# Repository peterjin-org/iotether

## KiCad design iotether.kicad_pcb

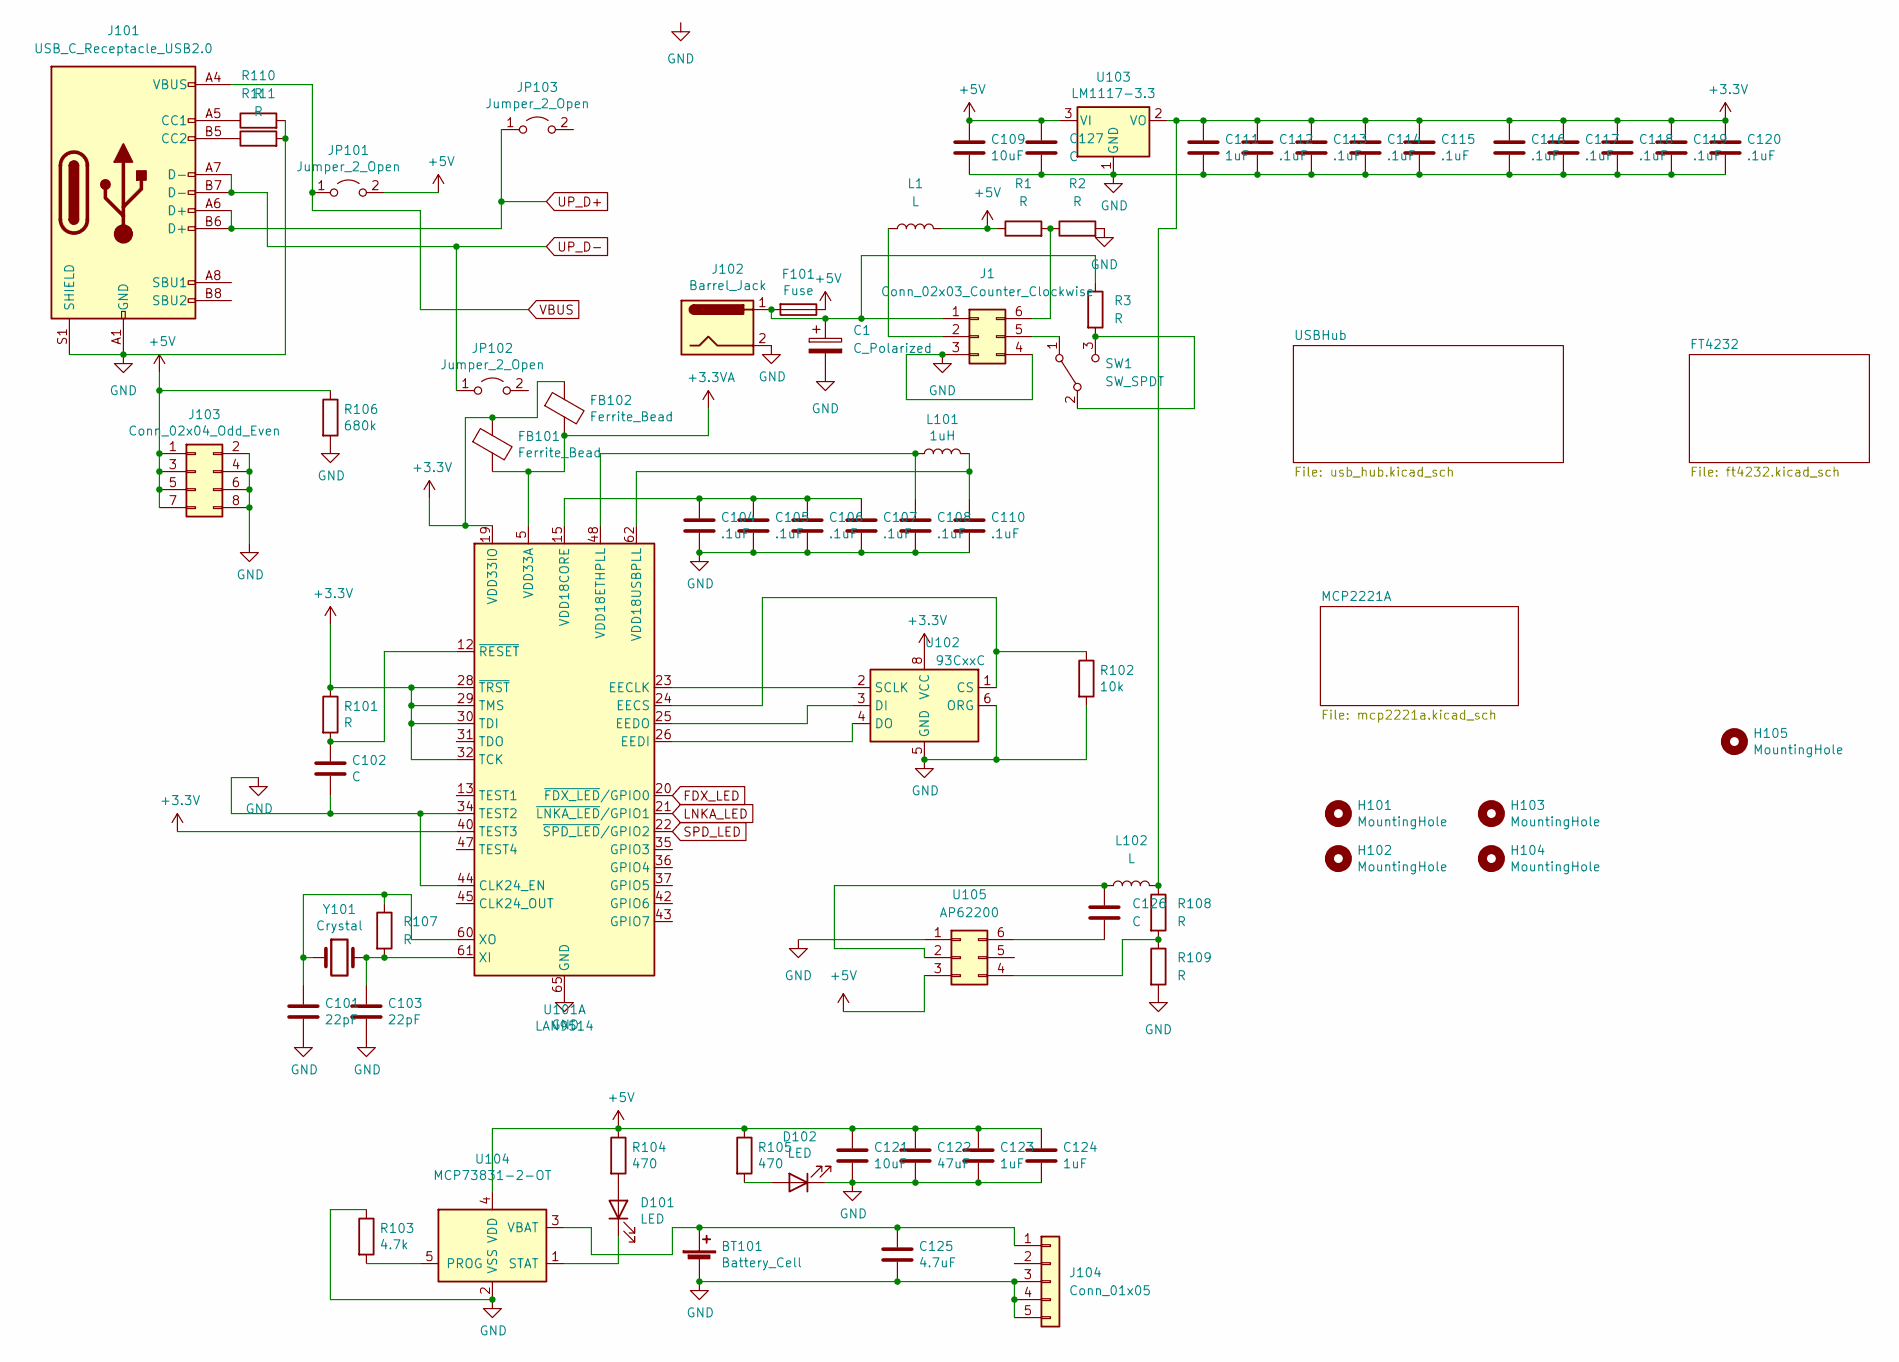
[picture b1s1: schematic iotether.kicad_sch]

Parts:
BT101: Battery_Cell; PinHeader_1x02_P2.54mm_Horizontal
C1: C_Polarized; CP_Radial_D10.0mm_P5.00mm
C101, C103: 22pF; C_0805_2012Metric_Pad1.15x1.40mm_HandSolder
C102: C; C_0805_2012Metric_Pad1.15x1.40mm_HandSolder
C104, C106: .1uF; C_0603_1608Metric_Pad1.08x0.95mm_HandSolder
C105, C107, C108, C110, C112, C113, C114, C115, C116, C117, C118, C119, C120: .1uF; C_0603_1608Metric_Pad1.05x0.95mm_HandSolder
C109: 10uF; C_0805_2012Metric_Pad1.15x1.40mm_HandSolder
C111: 1uF; C_0805_2012Metric_Pad1.15x1.40mm_HandSolder
C121: 10uF; CP_Radial_D8.0mm_P3.50mm
C122: 47uF; CP_Radial_D8.0mm_P3.50mm
C123, C124: 1uF; CP_Radial_D8.0mm_P3.50mm
C125: 4.7uF; CP_Radial_D6.3mm_P2.50mm
C126: C; C_0603_1608Metric
C127: C; CP_Radial_D8.0mm_P3.80mm
D101, D102: LED; LED_1210_3225Metric_Pad1.42x2.65mm_HandSolder
F101: Fuse; Fuse_BelFuse_0ZRE0033FF_L11.4mm_W3.8mm
FB101, FB102: Ferrite_Bead; L_1206_3216Metric_Pad1.22x1.90mm_HandSolder
H101, H102, H103, H104: MountingHole; MountingHole_3.2mm_M3
H105: MountingHole; OSHW-Logo2_7.3x6mm_SilkScreen
J1: Conn_02x03_Counter_Clockwise; SOT-563
J101: USB_C_Receptacle_USB2.0; USB_C_Receptacle_GCT_USB4105-xx-A_16P_TopMnt_Horizontal
J102: Barrel_Jack; BarrelJack_Horizontal
J103: Conn_02x04_Odd_Even; PinHeader_2x04_P2.54mm_Vertical
J104: Conn_01x05; 009155003541006
JP101, JP102, JP103: Jumper_2_Open; R_0603_1608Metric
L1: L; L_Radial_D12.5mm_P7.00mm_Fastron_09HCP
L101: 1uH; L_1206_3216Metric_Pad1.42x1.75mm_HandSolder
L102: L; L_1210_3225Metric_Pad1.42x2.65mm_HandSolder
R1, R2, R3, R108, R109, R110, R111: R; R_0603_1608Metric
R101: R; R_0603_1608Metric_Pad1.05x0.95mm_HandSolder
R102: 10k; R_0603_1608Metric_Pad1.05x0.95mm_HandSolder
R103: 4.7k; R_0603_1608Metric_Pad1.05x0.95mm_HandSolder
R104, R105: 470; R_0603_1608Metric_Pad1.05x0.95mm_HandSolder
R106: 680k; R_0603_1608Metric_Pad0.98x0.95mm_HandSolder
R107: R; R_0805_2012Metric
SW1: SW_SPDT; PinSocket_1x03_P2.54mm_Vertical
U101: LAN9514; QFN-64-1EP_9x9mm_P0.5mm_EP6x6mm
U102: 93CxxC; DIP-8_W7.62mm_Socket
U103: LM1117-3.3; SOT-223-3_TabPin2
U104: MCP73831-2-OT; SOT-23-5
U105: AP62200; SOT-23-6
Y101: Crystal; Crystal_HC49-U_Vertical

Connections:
+3.3VA: FB101.2, FB102.2, U101.5 (VDD33A), U101.10 (VDD33A), U101.49 (VDD33A), U101.51 (VDD33A), U101.54 (VDD33A), U101.57 (VDD33A), U101.64 (VDD33A); also elsewhere on the board
+3V3: C111.1, C112.1, C113.1, C114.1, C115.1, C116.1, C117.1, C118.1, C119.1, C120.1, FB101.1, FB102.1, L102.2, R101.1, R108.1, U101.19 (VDD33IO), U101.27 (VDD33IO), U101.28 (~TRST), U101.29 (TMS), U101.30 (TDI), U101.32 (TCK), U101.33 (VDD33IO), U101.39 (VDD33IO), U101.40 (TEST3), U101.46 (VDD33IO), U102.8 (VCC), U103.2 (VO); also elsewhere on the board
+5V: C109.1, C121.1, C122.1, C123.1, C124.1, C127.1, F101.1, J103.1, J103.3, J103.5, J103.7, JP101.2 (B), L1.2, R1.1, R104.1, R105.1, R106.1, U103.3 (VI), U104.4 (VDD), U105.3; also elsewhere on the board
FDX_LED: U101.20 (~FDX_LED/GPIO0); also elsewhere on the board
GND: BT101.2 (-), C1.2, C101.2, C102.2, C103.2, C104.2, C105.2, C106.2, C107.2, C108.2, C109.2, C110.2, C111.2, C112.2, C113.2, C114.2, C115.2, C116.2, C117.2, C118.2, C119.2, C120.2, C121.2, C122.2, C123.2, C124.2, C125.2, C127.2, D102.1 (K), J1.3, J1.4, J101.A1 (GND), J101.A12 (GND), J101.B1 (GND), J101.B12 (GND), J101.S1 (SHIELD), J102.2, J103.2, J103.4, J103.6, J103.8, J104.3, J104.4, J104.5, R2.2, R102.2, R103.1, R106.2, R109.2, R110.2, R111.2, U101.34 (TEST2), U101.44 (CLK24_EN), U101.65 (GND), U102.5 (GND), U102.6 (ORG), U103.1 (GND), U104.2 (VSS), U105.1; also elsewhere on the board
LNKA_LED: U101.21 (~LNKA_LED/GPIO1); also elsewhere on the board
unnamed: BT101.1 (+), C125.1, J104.1, U104.3 (VBAT)
unnamed: C1.1, F101.2, J1.1, J102.1, R3.1
unnamed: C101.1, R107.1, U101.60 (XO), Y101.1
unnamed: C102.1, R101.2, U101.12 (~RESET)
unnamed: C103.1, R107.2, U101.61 (XI), Y101.2
unnamed: C104.1, C105.1, C106.1, C107.1, U101.15 (VDD18CORE), U101.38 (VDD18CORE)
unnamed: C108.1, L101.1, U101.48 (VDD18ETHPLL)
unnamed: C110.1, L101.2, U101.62 (VDD18USBPLL)
unnamed: C126.1, L102.1, U105.2
unnamed: C126.2, U105.6
unnamed: D101.1 (K), U104.1 (STAT)
unnamed: D101.2 (A), R104.2
unnamed: D102.2 (A), R105.2
unnamed: J1.2, L1.1
unnamed: J1.5, SW1.1 (A)
unnamed: J1.6, R1.2, R2.1
unnamed: J101.A5 (CC1), R110.1
unnamed: J101.B5 (CC2), R111.1
unnamed: R3.2, SW1.2 (B), SW1.3 (C)
unnamed: R102.1, U101.24 (EECS), U102.1 (CS)
unnamed: R103.2, U104.5 (PROG)
unnamed: R108.2, R109.1, U105.4
unnamed: U101.23 (EECLK), U102.2 (SCLK)
unnamed: U101.25 (EEDO), U102.3 (DI)
unnamed: U101.26 (EEDI), U102.4 (DO)
SPD_LED: U101.22 (~SPD_LED/GPIO2); also elsewhere on the board
UP_D+: J101.A6 (D+), J101.B6 (D+), JP103.1 (A); also elsewhere on the board
UP_D-: J101.A7 (D-), J101.B7 (D-), JP102.1 (A); also elsewhere on the board
VBUS: J101.A4 (VBUS), J101.A9 (VBUS), J101.B4 (VBUS), J101.B9 (VBUS), JP101.1 (A); also elsewhere on the board

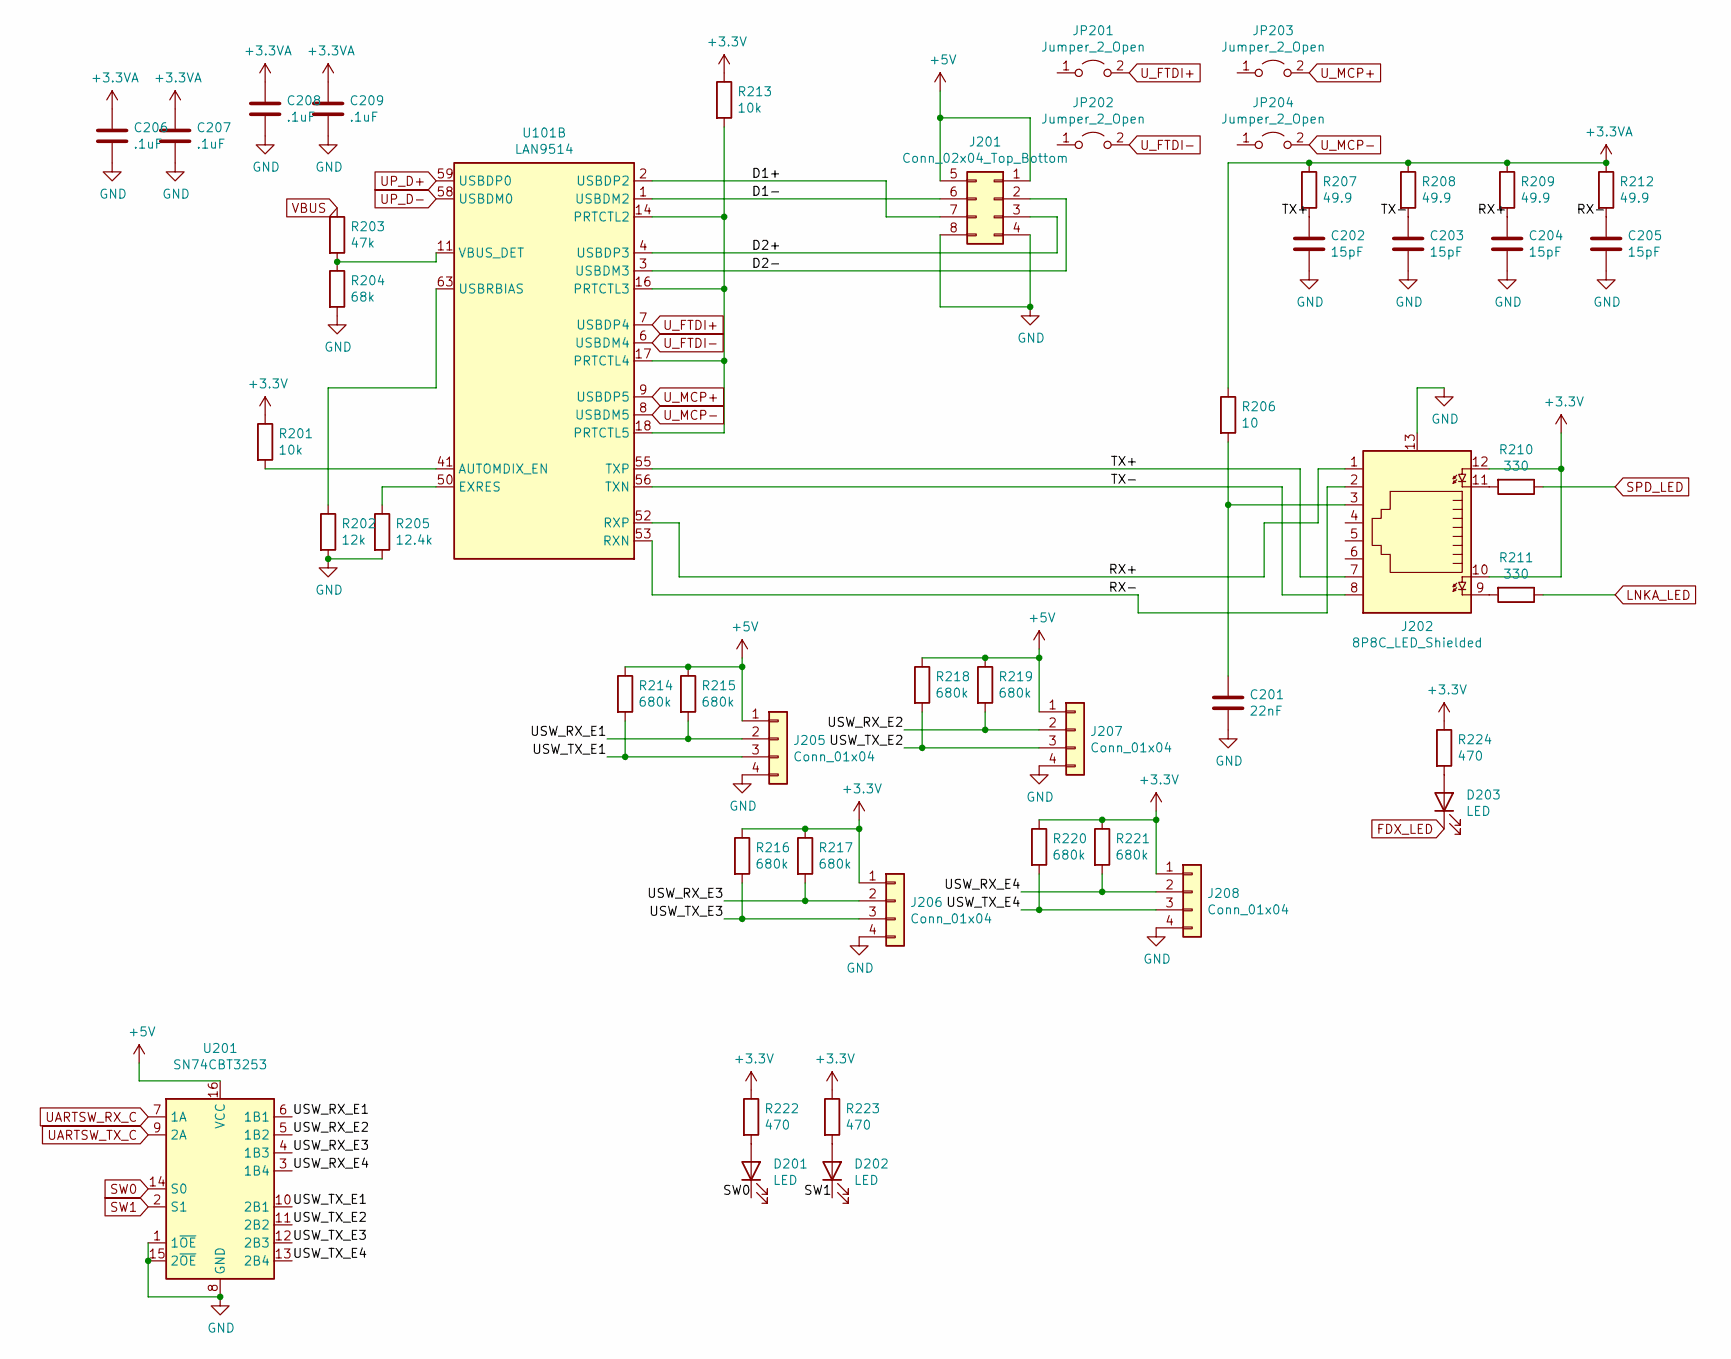
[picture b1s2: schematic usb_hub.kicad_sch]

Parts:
C201: 22nF; C_0603_1608Metric_Pad1.05x0.95mm_HandSolder
C202, C203, C204, C205: 15pF; C_0603_1608Metric_Pad1.05x0.95mm_HandSolder
C206, C207, C208, C209: .1uF; C_0603_1608Metric_Pad1.08x0.95mm_HandSolder
D201, D202, D203: LED; LED_0603_1608Metric_Pad1.05x0.95mm_HandSolder
J201: Conn_02x04_Top_Bottom; USB_A_Wuerth_61400826021_Horizontal_Stacked
J202: 8P8C_LED_Shielded; RJ45_Cetus_J1B1211CCD_Horizontal
J205, J206, J207, J208: Conn_01x04; PinHeader_1x04_P2.54mm_Vertical
JP201, JP202, JP203, JP204: Jumper_2_Open; R_0603_1608Metric
R201, R213: 10k; R_0603_1608Metric_Pad1.05x0.95mm_HandSolder
R202: 12k; R_0603_1608Metric_Pad1.05x0.95mm_HandSolder
R203: 47k; R_0603_1608Metric_Pad1.05x0.95mm_HandSolder
R204: 68k; R_0603_1608Metric_Pad1.05x0.95mm_HandSolder
R205: 12.4k; R_0603_1608Metric_Pad1.05x0.95mm_HandSolder
R206: 10; R_0603_1608Metric_Pad1.05x0.95mm_HandSolder
R207, R208, R209, R212: 49.9; R_0603_1608Metric_Pad1.05x0.95mm_HandSolder
R210, R211: 330; R_0603_1608Metric_Pad0.98x0.95mm_HandSolder
R214, R215, R216, R217, R218, R219, R220, R221: 680k; R_0603_1608Metric_Pad0.98x0.95mm_HandSolder
R222, R223, R224: 470; R_0603_1608Metric_Pad0.98x0.95mm_HandSolder
U101: LAN9514; QFN-64-1EP_9x9mm_P0.5mm_EP6x6mm
U201: SN74CBT3253; SOIC-16_3.9x9.9mm_P1.27mm

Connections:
+3.3VA: C206.1, C207.1, C208.1, C209.1, R206.1, R207.1, R208.1, R209.1, R212.1; also elsewhere on the board
+3V3: J202.10, J202.12, J206.1, J208.1, R201.1, R213.1, R216.1, R217.1, R220.1, R221.1, R222.1, R223.1, R224.1; also elsewhere on the board
+5V: J201.1, J201.5, J205.1, J207.1, R214.1, R215.1, R218.1, R219.1, U201.16 (VCC); also elsewhere on the board
/USBHub/D1+: J201.7, U101.2 (USBDP2)
/USBHub/D1-: J201.6, U101.1 (USBDM2)
/USBHub/D2+: J201.3, U101.4 (USBDP3)
/USBHub/D2-: J201.2, U101.3 (USBDM3)
/USBHub/RX+: C204.1, J202.1, R209.2, U101.52 (RXP)
/USBHub/RX-: C205.1, J202.2, R212.2, U101.53 (RXN)
/USBHub/TX+: C202.1, J202.7, R207.2, U101.55 (TXP)
/USBHub/TX-: C203.1, J202.8, R208.2, U101.56 (TXN)
/USBHub/USW_RX_E1: J205.2, R215.2, U201.6 (1B1)
/USBHub/USW_RX_E2: J207.2, R219.2, U201.5 (1B2)
/USBHub/USW_RX_E3: J206.2, R217.2, U201.4 (1B3)
/USBHub/USW_RX_E4: J208.2, R221.2, U201.3 (1B4)
/USBHub/USW_TX_E1: J205.3, R214.2, U201.10 (2B1)
/USBHub/USW_TX_E2: J207.3, R218.2, U201.11 (2B2)
/USBHub/USW_TX_E3: J206.3, R216.2, U201.12 (2B3)
/USBHub/USW_TX_E4: J208.3, R220.2, U201.13 (2B4)
FDX_LED: D203.1 (K); also elsewhere on the board
GND: C201.2, C202.2, C203.2, C204.2, C205.2, C206.2, C207.2, C208.2, C209.2, J201.4, J201.8, J202.13, J205.4, J206.4, J207.4, J208.4, R202.2, R204.2, R205.2, U201.1 (1~OE), U201.8 (GND), U201.15 (2~OE); also elsewhere on the board
LNKA_LED: R211.1; also elsewhere on the board
unnamed: C201.1, J202.3, R206.2
unnamed: D201.2 (A), R222.2
unnamed: D202.2 (A), R223.2
unnamed: D203.2 (A), R224.2
unnamed: J202.9, R211.2
unnamed: J202.11, R210.2
unnamed: R201.2, U101.41 (AUTOMDIX_EN)
unnamed: R202.1, U101.63 (USBRBIAS)
unnamed: R203.2, R204.1, U101.11 (VBUS_DET)
unnamed: R205.1, U101.50 (EXRES)
unnamed: R213.2, U101.14 (PRTCTL2), U101.16 (PRTCTL3), U101.17 (PRTCTL4), U101.18 (PRTCTL5)
SPD_LED: R210.1; also elsewhere on the board
SW0: D201.1 (K), U201.14 (S0); also elsewhere on the board
SW1: D202.1 (K), U201.2 (S1); also elsewhere on the board
UARTSW_RX_C: U201.7 (1A); also elsewhere on the board
UARTSW_TX_C: U201.9 (2A); also elsewhere on the board
UP_D+: U101.59 (USBDP0); also elsewhere on the board
UP_D-: U101.58 (USBDM0); also elsewhere on the board
U_FTDI+: JP201.2 (B), U101.7 (USBDP4); also elsewhere on the board
U_FTDI-: JP202.2 (B), U101.6 (USBDM4); also elsewhere on the board
U_MCP+: JP203.2 (B), U101.9 (USBDP5); also elsewhere on the board
U_MCP-: JP204.2 (B), U101.8 (USBDM5); also elsewhere on the board
VBUS: R203.1; also elsewhere on the board

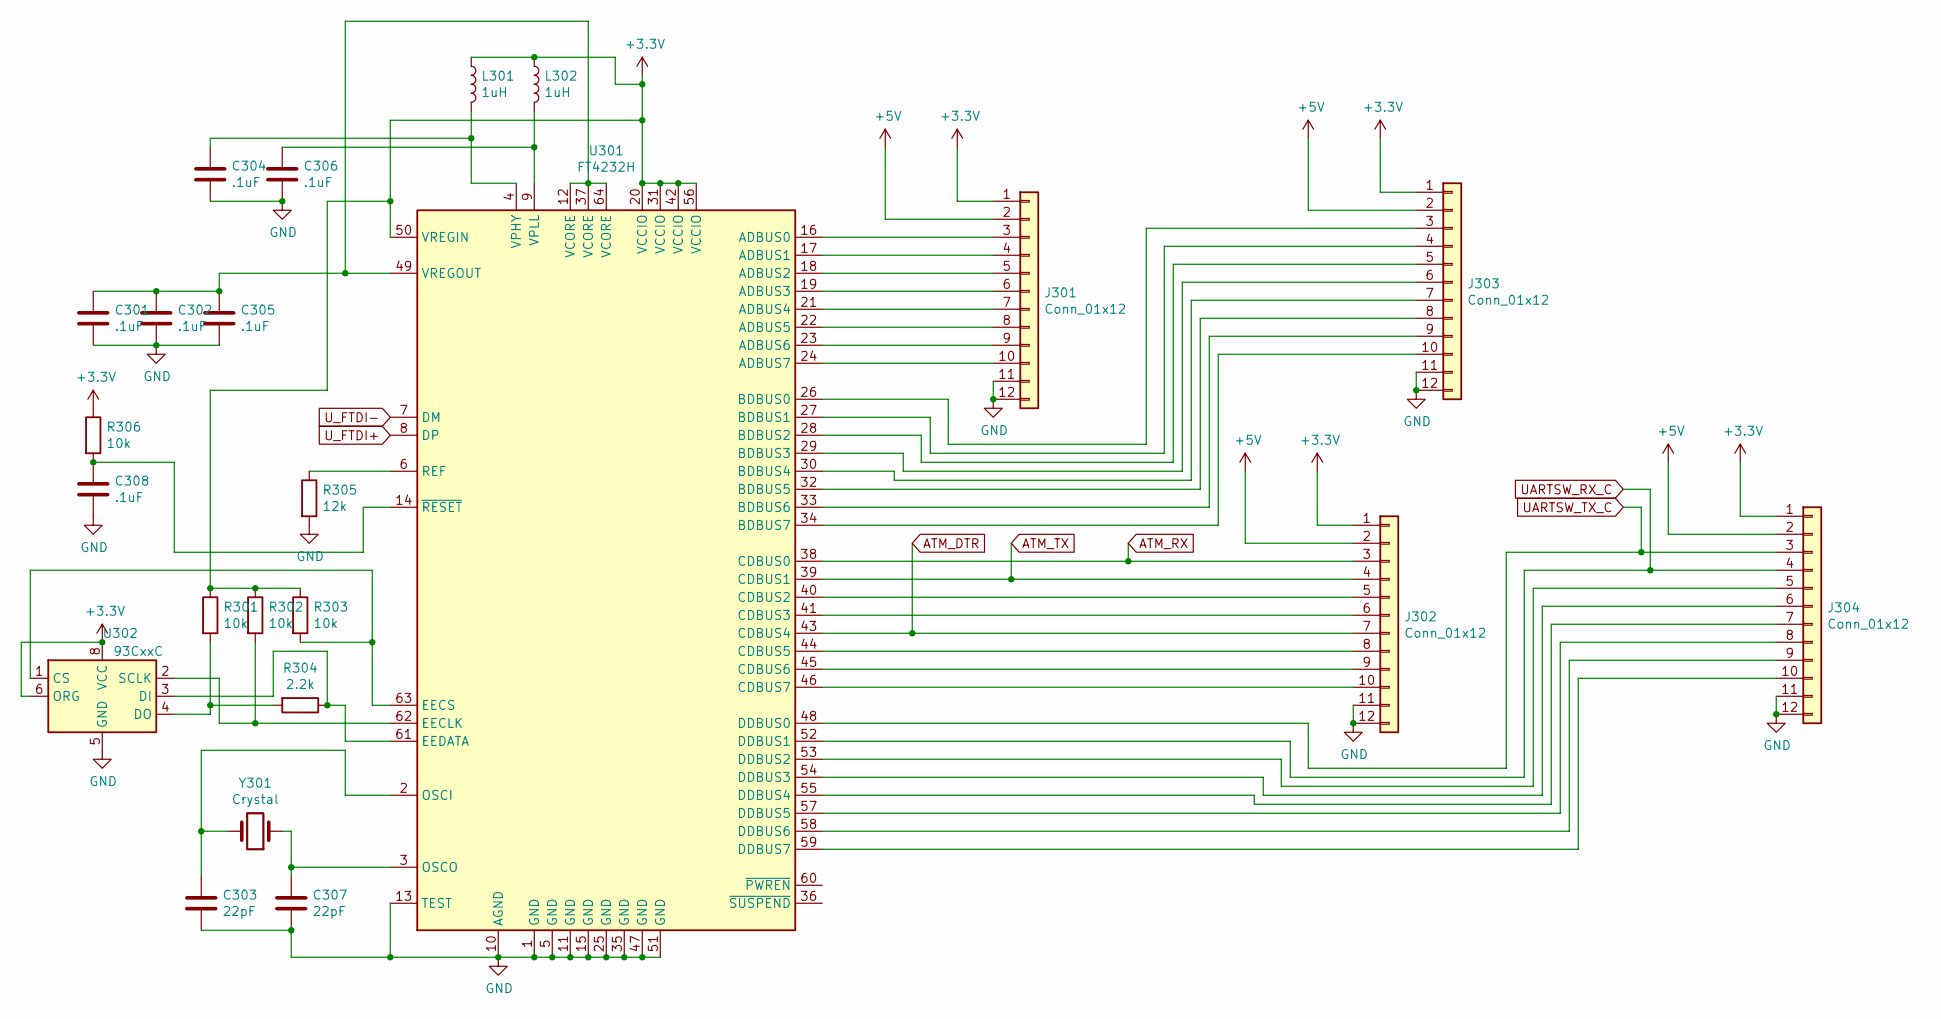
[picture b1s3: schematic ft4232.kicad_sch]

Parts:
C301, C302, C304, C305, C306, C308: .1uF; C_0603_1608Metric_Pad1.05x0.95mm_HandSolder
C303, C307: 22pF; C_0805_2012Metric_Pad1.15x1.40mm_HandSolder
J301, J302, J303, J304: Conn_01x12; PinHeader_2x06_P2.54mm_Vertical
L301, L302: 1uH; L_1206_3216Metric_Pad1.42x1.75mm_HandSolder
R301, R302, R303, R306: 10k; R_0603_1608Metric_Pad1.05x0.95mm_HandSolder
R304: 2.2k; R_0603_1608Metric_Pad0.98x0.95mm_HandSolder
R305: 12k; R_0603_1608Metric_Pad1.05x0.95mm_HandSolder
U301: FT4232H; LQFP-64_10x10mm_P0.5mm
U302: 93CxxC; DIP-8_W7.62mm_Socket
Y301: Crystal; Crystal_HC49-U_Vertical

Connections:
+3V3: J301.1, J302.1, J303.1, J304.1, L301.1, L302.1, R301.1, R302.1, R303.1, R306.1, U301.20 (VCCIO), U301.31 (VCCIO), U301.42 (VCCIO), U301.50 (VREGIN), U301.56 (VCCIO), U302.6 (ORG), U302.8 (VCC); also elsewhere on the board
+5V: J301.2, J302.2, J303.2, J304.2; also elsewhere on the board
ATM_DTR: J302.7, U301.43 (CDBUS4); also elsewhere on the board
ATM_RX: J302.3, U301.38 (CDBUS0); also elsewhere on the board
ATM_TX: J302.4, U301.39 (CDBUS1); also elsewhere on the board
GND: C301.2, C302.2, C303.2, C304.2, C305.2, C306.2, C307.2, C308.2, J301.11, J301.12, J302.11, J302.12, J303.11, J303.12, J304.11, J304.12, R305.2, U301.1 (GND), U301.5 (GND), U301.10 (AGND), U301.11 (GND), U301.13 (TEST), U301.15 (GND), U301.25 (GND), U301.35 (GND), U301.47 (GND), U301.51 (GND), U302.5 (GND); also elsewhere on the board
unnamed: C301.1, C302.1, C305.1, U301.12 (VCORE), U301.37 (VCORE), U301.49 (VREGOUT), U301.64 (VCORE)
unnamed: C303.1, U301.2 (OSCI), Y301.2
unnamed: C304.1, L301.2, U301.4 (VPHY)
unnamed: C306.1, L302.2, U301.9 (VPLL)
unnamed: C307.1, U301.3 (OSCO), Y301.1
unnamed: C308.1, R306.2, U301.14 (~RESET)
unnamed: J301.3, U301.16 (ADBUS0)
unnamed: J301.4, U301.17 (ADBUS1)
unnamed: J301.5, U301.18 (ADBUS2)
unnamed: J301.6, U301.19 (ADBUS3)
unnamed: J301.7, U301.21 (ADBUS4)
unnamed: J301.8, U301.22 (ADBUS5)
unnamed: J301.9, U301.23 (ADBUS6)
unnamed: J301.10, U301.24 (ADBUS7)
unnamed: J302.5, U301.40 (CDBUS2)
unnamed: J302.6, U301.41 (CDBUS3)
unnamed: J302.8, U301.44 (CDBUS5)
unnamed: J302.9, U301.45 (CDBUS6)
unnamed: J302.10, U301.46 (CDBUS7)
unnamed: J303.3, U301.26 (BDBUS0)
unnamed: J303.4, U301.27 (BDBUS1)
unnamed: J303.5, U301.28 (BDBUS2)
unnamed: J303.6, U301.29 (BDBUS3)
unnamed: J303.7, U301.30 (BDBUS4)
unnamed: J303.8, U301.32 (BDBUS5)
unnamed: J303.9, U301.33 (BDBUS6)
unnamed: J303.10, U301.34 (BDBUS7)
unnamed: J304.5, U301.53 (DDBUS2)
unnamed: J304.6, U301.54 (DDBUS3)
unnamed: J304.7, U301.55 (DDBUS4)
unnamed: J304.8, U301.57 (DDBUS5)
unnamed: J304.9, U301.58 (DDBUS6)
unnamed: J304.10, U301.59 (DDBUS7)
unnamed: R301.2, R304.2, U302.4 (DO)
unnamed: R302.2, U301.62 (EECLK), U302.2 (SCLK)
unnamed: R303.2, U301.63 (EECS), U302.1 (CS)
unnamed: R304.1, U301.61 (EEDATA), U302.3 (DI)
unnamed: R305.1, U301.6 (REF)
UARTSW_RX_C: J304.4, U301.52 (DDBUS1); also elsewhere on the board
UARTSW_TX_C: J304.3, U301.48 (DDBUS0); also elsewhere on the board
U_FTDI+: U301.8 (DP); also elsewhere on the board
U_FTDI-: U301.7 (DM); also elsewhere on the board

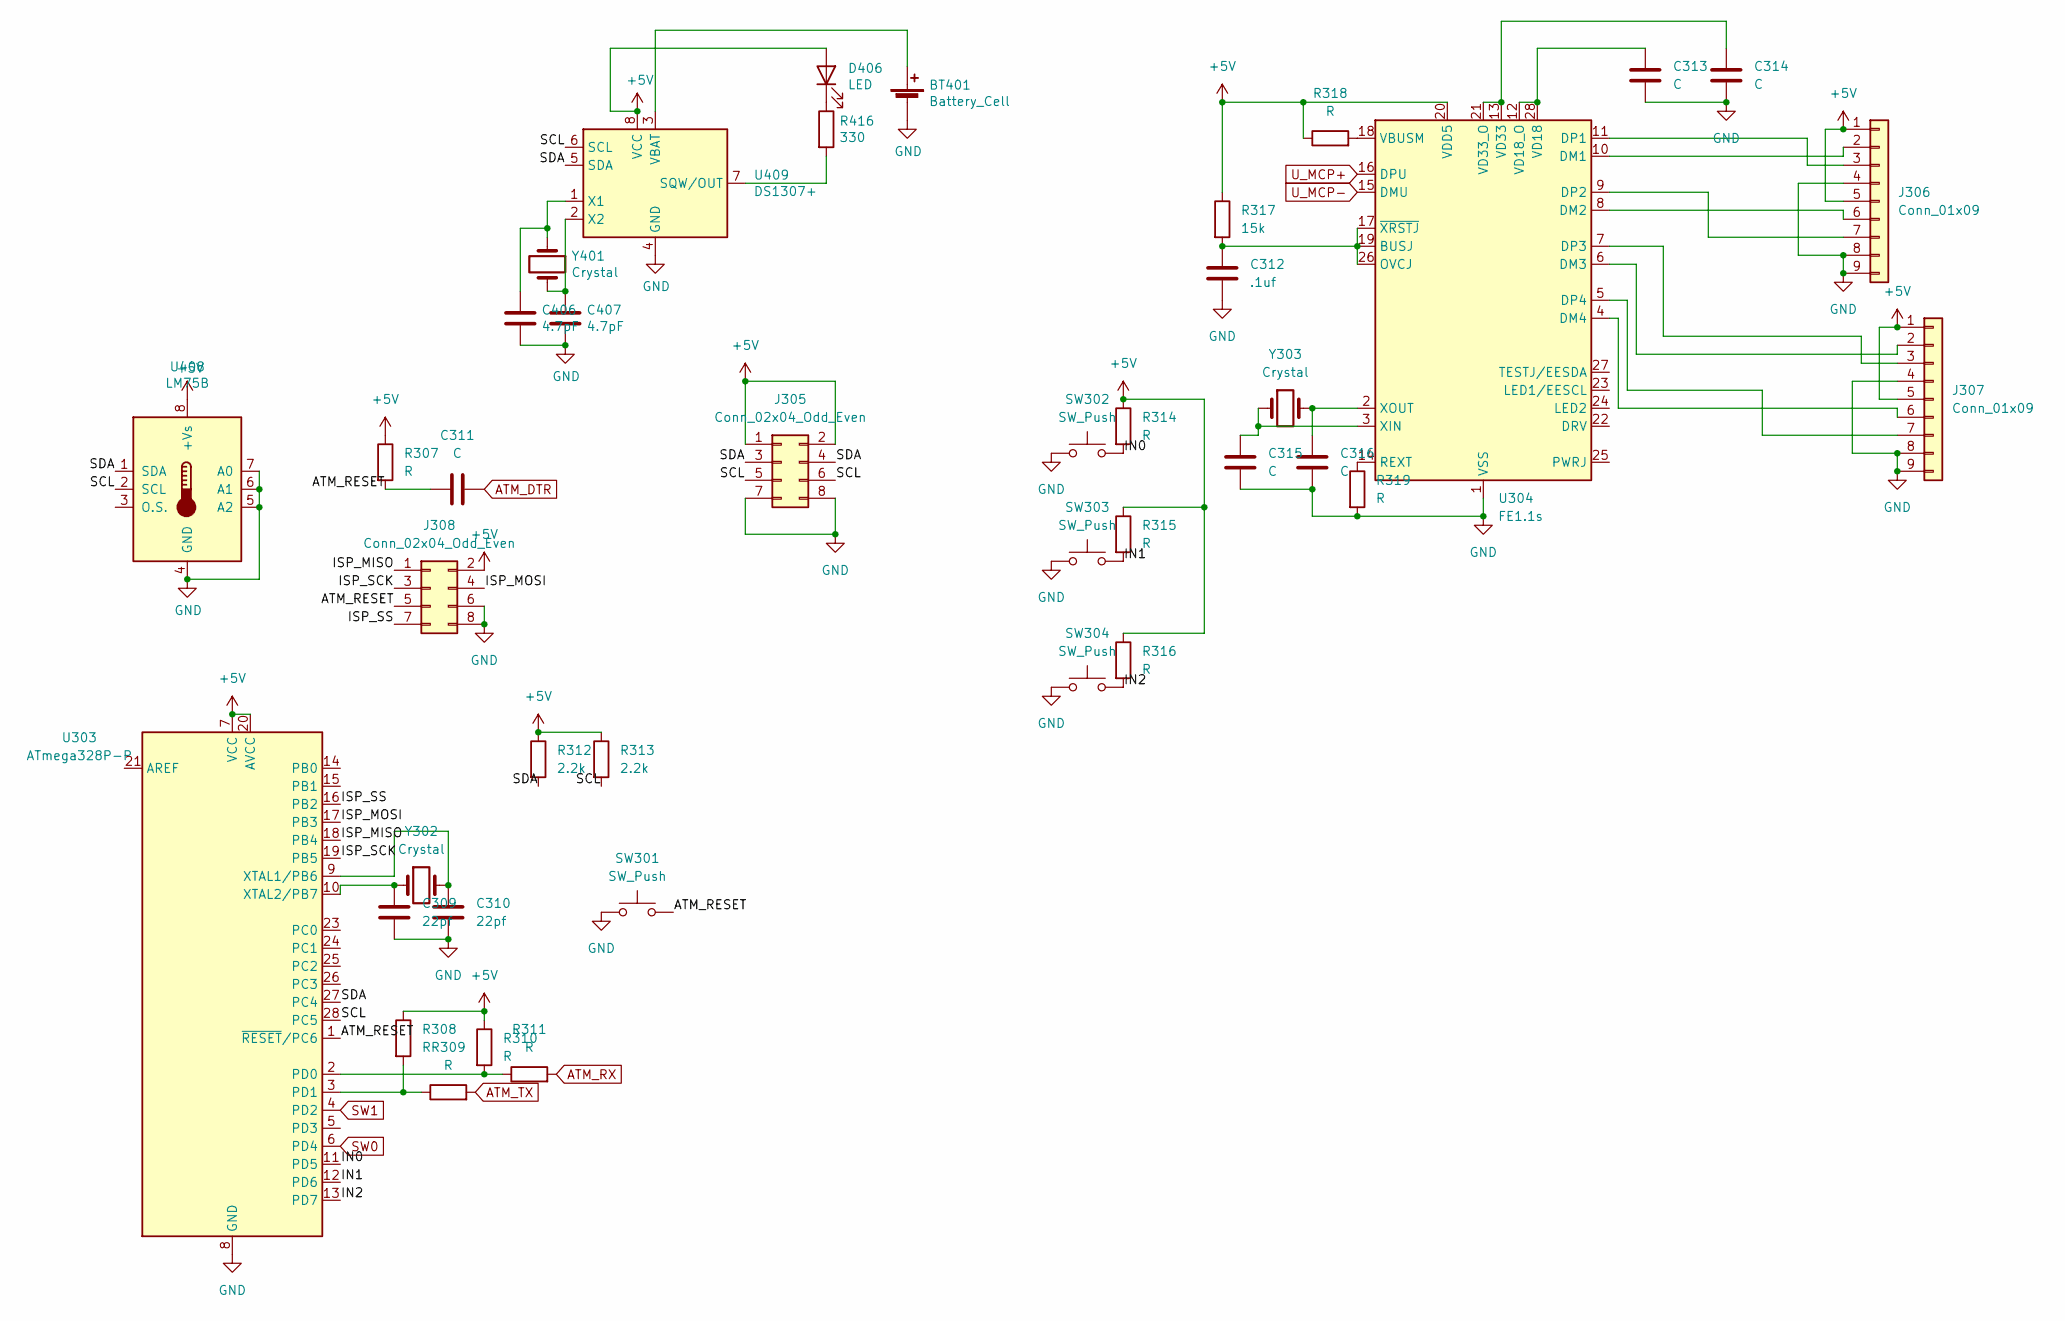
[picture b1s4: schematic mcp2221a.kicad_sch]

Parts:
BT401: Battery_Cell; PinHeader_1x02_P2.54mm_Vertical
C309, C310: 22pf; C_0805_2012Metric_Pad1.18x1.45mm_HandSolder
C311: C; C_0603_1608Metric_Pad1.08x0.95mm_HandSolder
C312: .1uf; C_0603_1608Metric_Pad1.08x0.95mm_HandSolder
C313, C314, C315, C316: C; C_0805_2012Metric_Pad1.18x1.45mm_HandSolder
C406, C407: 4.7pF; C_0603_1608Metric_Pad1.08x0.95mm_HandSolder
D406: LED; LED_0603_1608Metric_Pad1.05x0.95mm_HandSolder
J305, J308: Conn_02x04_Odd_Even; PinHeader_2x04_P2.54mm_Vertical
J306, J307: Conn_01x09; USB_A_Wuerth_61400826021_Horizontal_Stacked
R307, R308, R309, R310, R311, R314, R315, R316, R318, R319: R; R_0603_1608Metric_Pad0.98x0.95mm_HandSolder
R312, R313: 2.2k; R_0603_1608Metric_Pad0.98x0.95mm_HandSolder
R317: 15k; R_0603_1608Metric_Pad0.98x0.95mm_HandSolder
R416: 330; R_0603_1608Metric_Pad0.98x0.95mm_HandSolder
SW301, SW302, SW303, SW304: SW_Push; SW_PUSH_6mm
U303: ATmega328P-P; DIP-28_W7.62mm
U304: FE1.1s; SSOP-28_3.9x9.9mm_P0.635mm
U408: LM75B; SOIC-8_3.9x4.9mm_P1.27mm
U409: DS1307+; SOIC-8_3.9x4.9mm_P1.27mm
Y302, Y303: Crystal; Crystal_HC49-U_Vertical
Y401: Crystal; Crystal_C26-LF_D2.1mm_L6.5mm_Horizontal

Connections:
+5V: D406.2 (A), J305.1, J305.2, J306.1, J306.5, J307.1, J307.5, J308.2, R307.1, R308.1, R310.1, R312.1, R313.1, R314.1, R315.1, R316.1, R317.1, R318.1, U303.7 (VCC), U303.20 (AVCC), U304.20 (VDD5), U408.8 (+Vs), U409.8 (VCC); also elsewhere on the board
/MCP2221A/ATM_RESET: C311.1, J308.5, R307.2, SW301.2, U303.1 (~RESET/PC6)
/MCP2221A/IN0: R314.2, SW302.2, U303.11 (PD5)
/MCP2221A/IN1: R315.2, SW303.2, U303.12 (PD6)
/MCP2221A/IN2: R316.2, SW304.2, U303.13 (PD7)
/MCP2221A/ISP_MISO: J308.1, U303.18 (PB4)
/MCP2221A/ISP_MOSI: J308.4, U303.17 (PB3)
/MCP2221A/ISP_SCK: J308.3, U303.19 (PB5)
/MCP2221A/ISP_SS: J308.7, U303.16 (PB2)
/MCP2221A/SCL: J305.5, J305.6, R313.2, U303.28 (PC5), U408.2 (SCL), U409.6 (SCL)
/MCP2221A/SDA: J305.3, J305.4, R312.2, U303.27 (PC4), U408.1 (SDA), U409.5 (SDA)
ATM_DTR: C311.2; also elsewhere on the board
ATM_RX: R311.2; also elsewhere on the board
ATM_TX: R309.2; also elsewhere on the board
GND: BT401.2 (-), C309.2, C310.2, C312.2, C313.2, C314.2, C315.2, C316.2, C406.2, C407.2, J305.7, J305.8, J306.4, J306.8, J306.9, J307.4, J307.8, J307.9, J308.6, J308.8, R319.2, SW301.1, SW302.1, SW303.1, SW304.1, U303.8 (GND), U303.22 (GND), U304.1 (VSS), U408.4 (GND), U408.5 (A2), U408.6 (A1), U408.7 (A0), U409.4 (GND); also elsewhere on the board
unnamed: BT401.1 (+), U409.3 (VBAT)
unnamed: C309.1, U303.10 (XTAL2/PB7), Y302.1
unnamed: C310.1, U303.9 (XTAL1/PB6), Y302.2
unnamed: C312.1, R317.2, U304.17 (~XRSTJ), U304.19 (BUSJ), U304.26 (OVCJ)
unnamed: C313.1, U304.12 (VD18_O), U304.28 (VD18)
unnamed: C314.1, U304.13 (VD33), U304.21 (VD33_O)
unnamed: C315.1, U304.3 (XIN), Y303.1
unnamed: C316.1, U304.2 (XOUT), Y303.2
unnamed: C406.1, U409.1 (X1), Y401.1
unnamed: C407.1, U409.2 (X2), Y401.2
unnamed: D406.1 (K), R416.1
unnamed: J306.2, U304.10 (DM1)
unnamed: J306.3, U304.11 (DP1)
unnamed: J306.6, U304.8 (DM2)
unnamed: J306.7, U304.9 (DP2)
unnamed: J307.2, U304.6 (DM3)
unnamed: J307.3, U304.7 (DP3)
unnamed: J307.6, U304.4 (DM4)
unnamed: J307.7, U304.5 (DP4)
unnamed: R308.2, R309.1, U303.3 (PD1)
unnamed: R310.2, R311.1, U303.2 (PD0)
unnamed: R318.2, U304.18 (VBUSM)
unnamed: R319.1, U304.14 (REXT)
unnamed: R416.2, U409.7 (SQW/OUT)
SW0: U303.6 (PD4); also elsewhere on the board
SW1: U303.4 (PD2); also elsewhere on the board
U_MCP+: U304.16 (DPU); also elsewhere on the board
U_MCP-: U304.15 (DMU); also elsewhere on the board

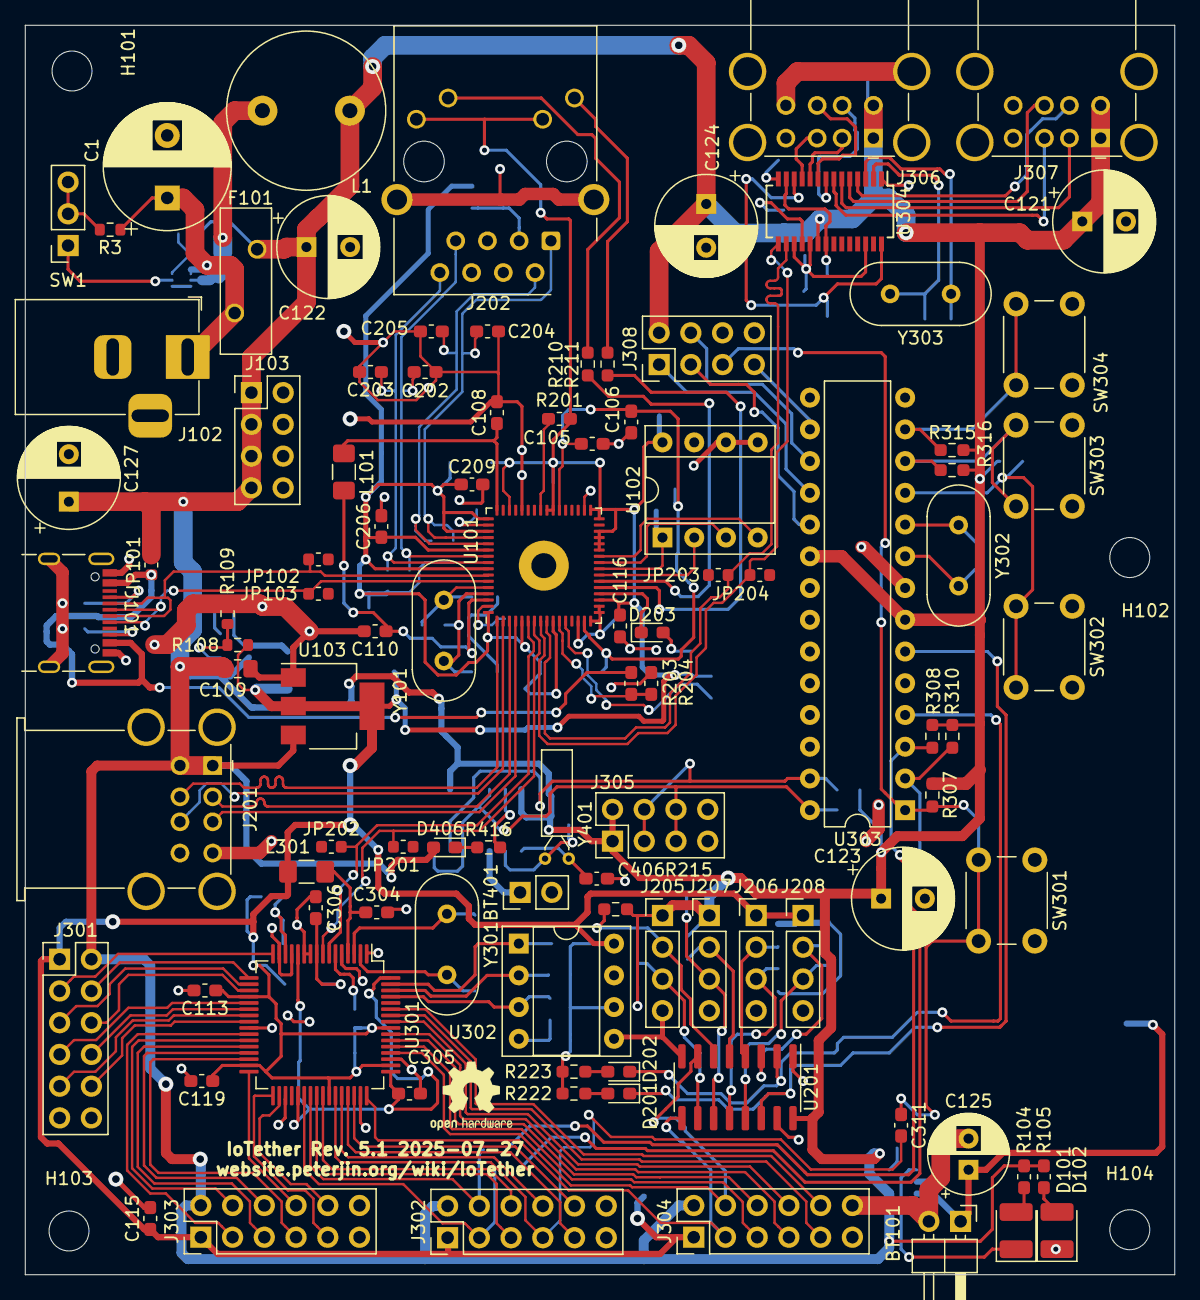
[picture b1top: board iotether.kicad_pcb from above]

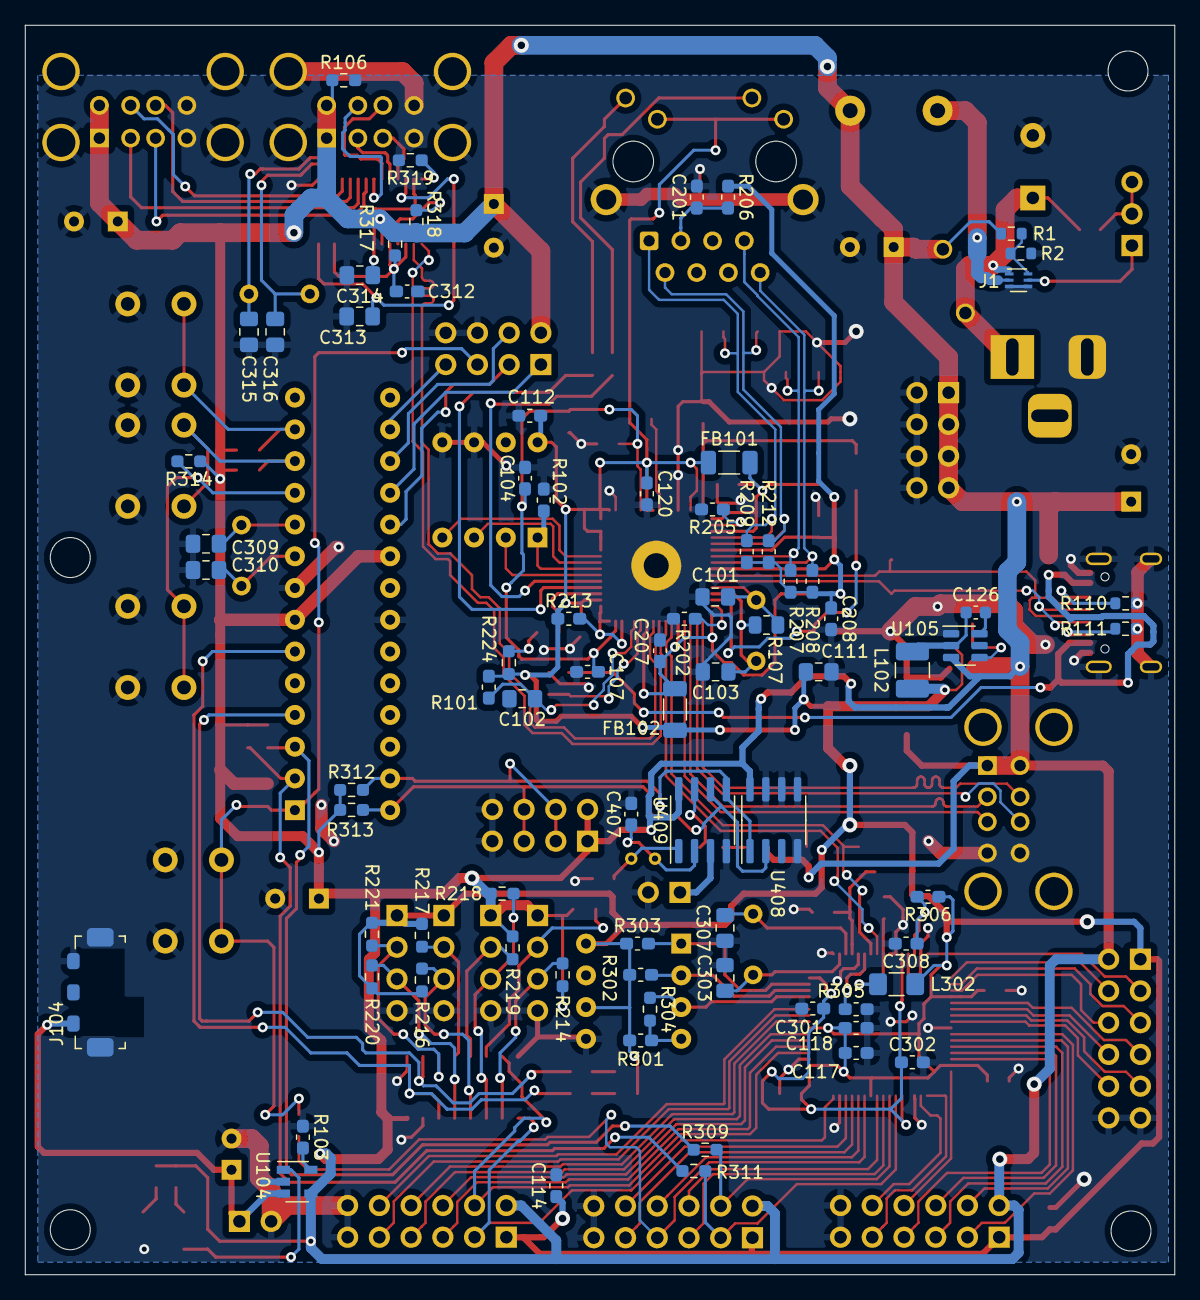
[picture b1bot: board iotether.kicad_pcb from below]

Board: 2 copper layers, 92.0 x 100.0 mm, 182 parts (77 on the bottom side), 145 nets.
